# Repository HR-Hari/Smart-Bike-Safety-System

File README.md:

# Smart Bike Safety System

A **Smart Bike Safety System** for motor bikes using a **dual-microcontroller architecture**.  
The system detects theft attempts, abnormal movement, crash events, and **rider alcohol consumption**, sends **real-time alerts with GPS location** to the owner via **GSM**, and can **remotely disable the engine** for enhanced safety and security.

## Project Overview

Motor bike theft, unsafe riding, and delayed accident response remain major challenges.  
This project presents a **smart embedded safety and anti-theft solution** using **ESP32-based controllers**, inertial sensing, alcohol detection, GPS tracking, and GSM communication.

The system is divided into:

- **Master Unit (ESP32)** – Handles GPS tracking, GSM communication, crash detection, theft response, and engine cutoff.  
- **Slave Unit (ESP32-C3 Mini)** – Dedicated to rider safety monitoring, including alcohol detection and environmental sensing.

This modular design improves **reliability, power efficiency, fault isolation, and scalability**.

## System Functionality & Working

The Smart Bike Safety System operates using a **distributed dual-controller architecture** to ensure reliable monitoring and fast response. The **ESP32 Master unit**, powered directly from the bike battery, acts as the central control node responsible for decision-making, communication, and engine control. It interfaces with a **SIM900A GSM module** for SMS alerts, a **NEO-M8N GPS module** for real-time location tracking, a **5V relay** for engine cutoff, and an **MPU6050 inertial sensor** for detecting crash events and abnormal vehicle motion.

A secondary **ESP32-C3 Mini Slave unit**, powered by a rechargeable 5V battery, focuses on **rider safety monitoring**. It continuously measures alcohol concentration using the **MQ-3 alcohol sensor** and environmental conditions using the **DHT22 temperature and humidity sensor**. The Slave unit communicates safety status data wirelessly to the Master using **ESP-NOW**, enabling low-latency and power-efficient data transfer without relying on external networks.

During operation, the system continuously evaluates inputs from both controllers. If **alcohol consumption exceeds a predefined threshold**, a **crash is detected**, or **unauthorized movement** is identified, the Master unit immediately retrieves GPS coordinates and sends an **SMS alert via GSM** to the registered user. In critical scenarios, the system activates the **engine cutoff relay**, preventing the bike from being started or continuing operation. This integrated approach ensures **theft prevention, rider safety, and rapid incident notification** in a single embedded solution.

## Objectives

- Detect unauthorized movement or theft attempts  
- Detect crash events using inertial sensing  
- Detect rider alcohol consumption before or during riding  
- Send real-time SMS alerts with GPS location  
- Remotely disable the bike engine when unsafe conditions are detected  
- Implement a low-cost, embedded IoT-based safety system  

## System Architecture
            ┌────────────────────────────┐
            │        ESP32 MASTER        │
            │─────────────────────────── │
            │ • GSM (SIM900A)            │
            │ • GPS (NEO-M8N)            │
            │ • MPU6050 (Crash Detection)│
            │ • Engine Cutoff Relay      │
            │ • Alert & Control Logic    │
            └───────────▲────────────────┘
                        │ ESP-NOW
            ┌───────────┴────────────────┐
            │       ESP32-C3 MINI SLAVE  │
            │────────────────────────────│
            │ • MQ-3 (Alcohol Detection) │
            │ • DHT22 (Temp & Humidity)  │
            │ • Rider Safety Monitoring  │
            └────────────────────────────┘

## Hardware Components

### Master Unit (ESP32)

| Component | Description |
|---------|------------|
| ESP32 | Main controller |
| SIM900A GSM Module | SMS alert communication |
| NEO-M8N GPS Module | Real-time location tracking |
| MPU6050 | Crash and abnormal motion detection |
| 5V Relay Module | Engine cutoff control |
| Power Source | Motor bike 12V battery (regulated) |

### Slave Unit (ESP32-C3 Mini)

| Component | Description |
|---------|------------|
| ESP32-C3 Mini | Secondary controller |
| MQ-3 Alcohol Sensor | Rider alcohol detection |
| DHT22 | Temperature & humidity monitoring |
| Power Source | 5V rechargeable battery |

## Schematic

## PCB & Enclosure Design

### Master Unit PCB Design
<table>
  <tr>
    <td>
      
    </td>
    <td>
      
    </td>
  </tr>
</table>

### Slave Unit PCB Design

<table>
  <tr>
    <td>
      
    </td>
    <td>
      
    </td>
  </tr>
</table>

### Master & Slave Enclosure / Casing

> **(Insert Master and Slave casing images here)**  
> *Show how the units are enclosed and protected for installation on the bike.*

## Software & Technologies

- **Programming Language**: C / C++
- **IDE**: Arduino IDE
- **Wireless Communication**:
  - ESP-NOW (ESP32 ↔ ESP32-C3)
- **Serial Communication**:
  - UART (ESP32 ↔ GSM)
  - UART (ESP32 ↔ GPS)
- **Core Concepts**:
  - Embedded Systems
  - IoT-based Vehicle Safety
  - Sensor Interfacing
  - Real-time Event Detection
  - Power Management

## Key Features

- Theft detection through abnormal motion analysis  
- Crash detection using MPU6050  
- Alcohol detection using MQ-3 sensor  
- Environmental monitoring using DHT22  
- GPS-based real-time location sharing  
- SMS alerts via GSM (SIM900A)  
- Engine immobilization using relay  
- Dual power supply for uninterrupted operation  

## Project Structure

## Testing & Validation

- Unauthorized movement and theft detection  
- Crash detection sensitivity tuning  
- Alcohol threshold calibration  
- GSM SMS delivery reliability  
- GPS fix accuracy and response time  
- Engine cutoff activation timing  

System validated under real motor bike operating conditions.

## Future Enhancements

- Mobile application integration  
- Cloud-based real-time tracking dashboard  
- Rider authentication using BLE or RFID  
- Geofencing alerts  
- AI-based rider behavior analysis

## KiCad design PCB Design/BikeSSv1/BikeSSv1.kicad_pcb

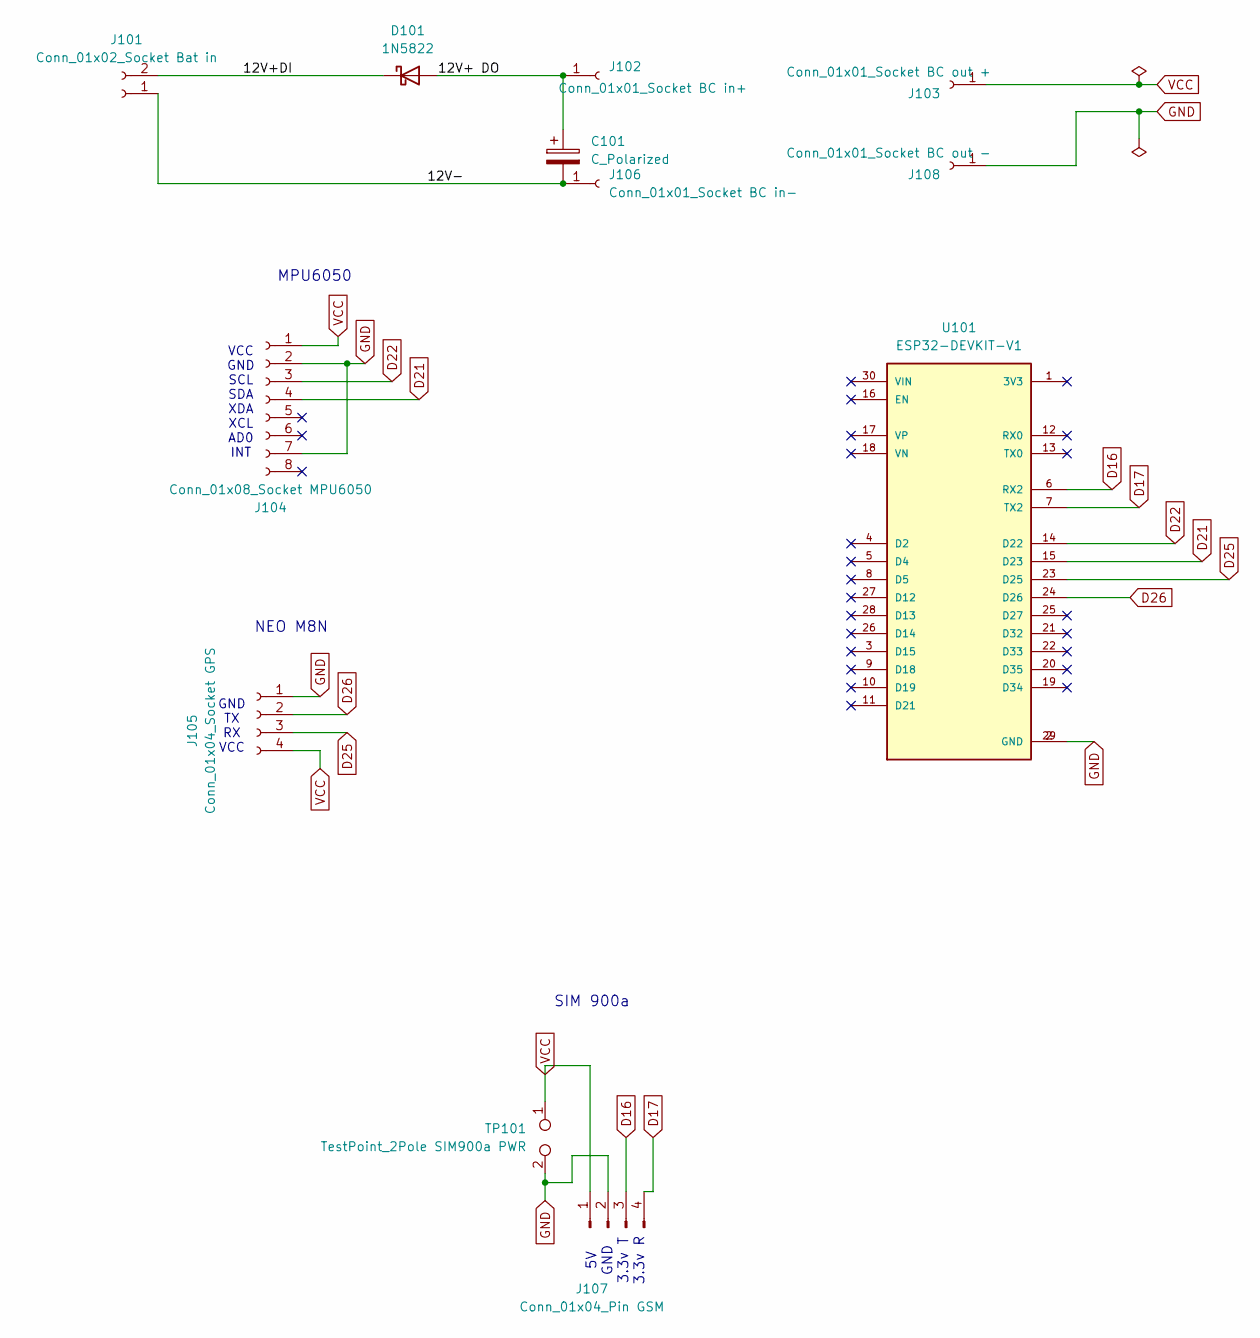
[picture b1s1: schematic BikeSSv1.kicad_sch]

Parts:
C101: C_Polarized; CP_Radial_D8.0mm_P3.50mm
D101: 1N5822; D_DO-201AD_P15.24mm_Horizontal
J101: Conn_01x02_Socket Bat in; JST_XH_B2B-XH-AM_1x02_P2.50mm_Vertical
J102: Conn_01x01_Socket BC in+; PinSocket_1x01_P2.54mm_Vertical
J103: Conn_01x01_Socket BC out +; PinSocket_1x01_P2.54mm_Vertical
J104: Conn_01x08_Socket MPU6050; PinSocket_1x08_P2.54mm_Vertical
J105: Conn_01x04_Socket GPS; PinSocket_1x04_P2.54mm_Vertical
J106: Conn_01x01_Socket BC in-; PinSocket_1x01_P2.54mm_Vertical
J107: Conn_01x04_Pin GSM; PinSocket_1x04_P2.54mm_Vertical
J108: Conn_01x01_Socket BC out -; PinSocket_1x01_P2.54mm_Vertical
TP101: TestPoint_2Pole SIM900a PWR; TestPoint_2Pads_Pitch5.08mm_Drill1.3mm
U101: ESP32-DEVKIT-V1; MODULE_ESP32_DEVKIT_V1; PARTREV N/A

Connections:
/12V+ DO: C101.1, D101.2 (A), J102.1
/12V+DI: D101.1 (K), J101.2
/12V-: C101.2, J101.1, J106.1
D16: J107.3, U101.6 (RX2)
D17: J107.4, U101.7 (TX2)
D21: J104.4, U101.15 (D23)
D22: J104.3, U101.14 (D22)
D25: J105.3, U101.23 (D25)
D26: J105.2, U101.24 (D26)
GND: J104.2, J104.7, J105.1, J107.2, J108.1, TP101.2, U101.2 (GND), U101.29 (GND)
VCC: J103.1, J104.1, J105.4, J107.1, TP101.1

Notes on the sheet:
VCC GND SCL SDA XDA XCL AD0 INT
5V GND 3.3v T 3.3v R
SIM 900a
NEO M8N
GND TX RX VCC
MPU6050

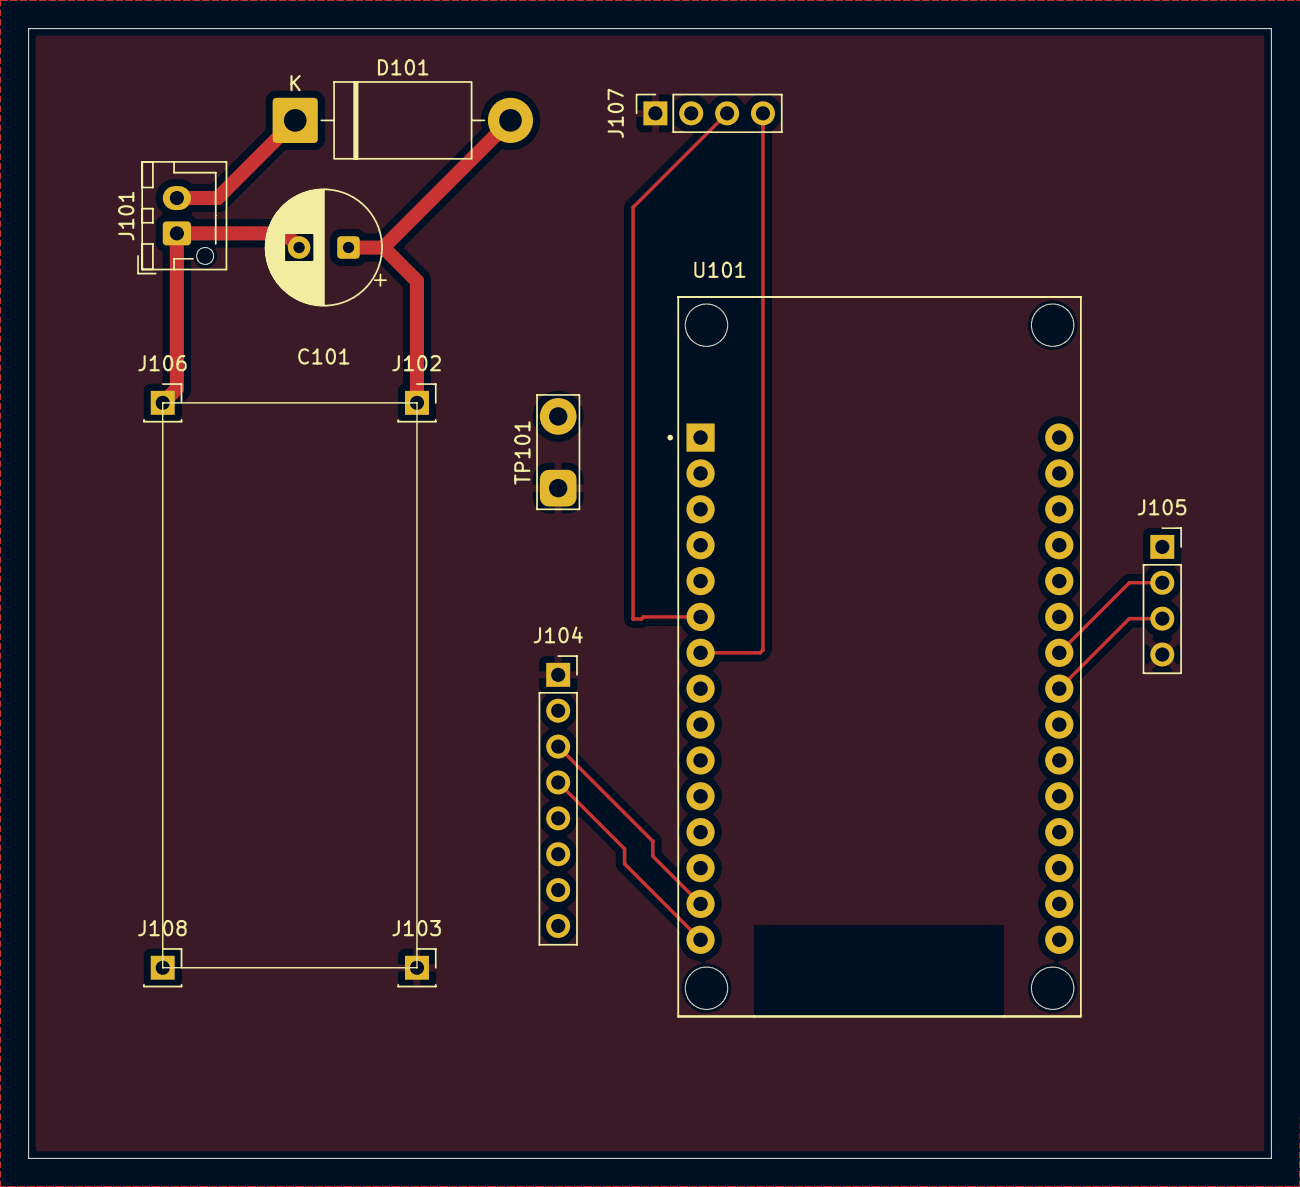
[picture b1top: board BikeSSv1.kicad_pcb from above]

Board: 2 copper layers, 88.0 x 80.0 mm, 12 parts (0 on the bottom side), 11 nets.

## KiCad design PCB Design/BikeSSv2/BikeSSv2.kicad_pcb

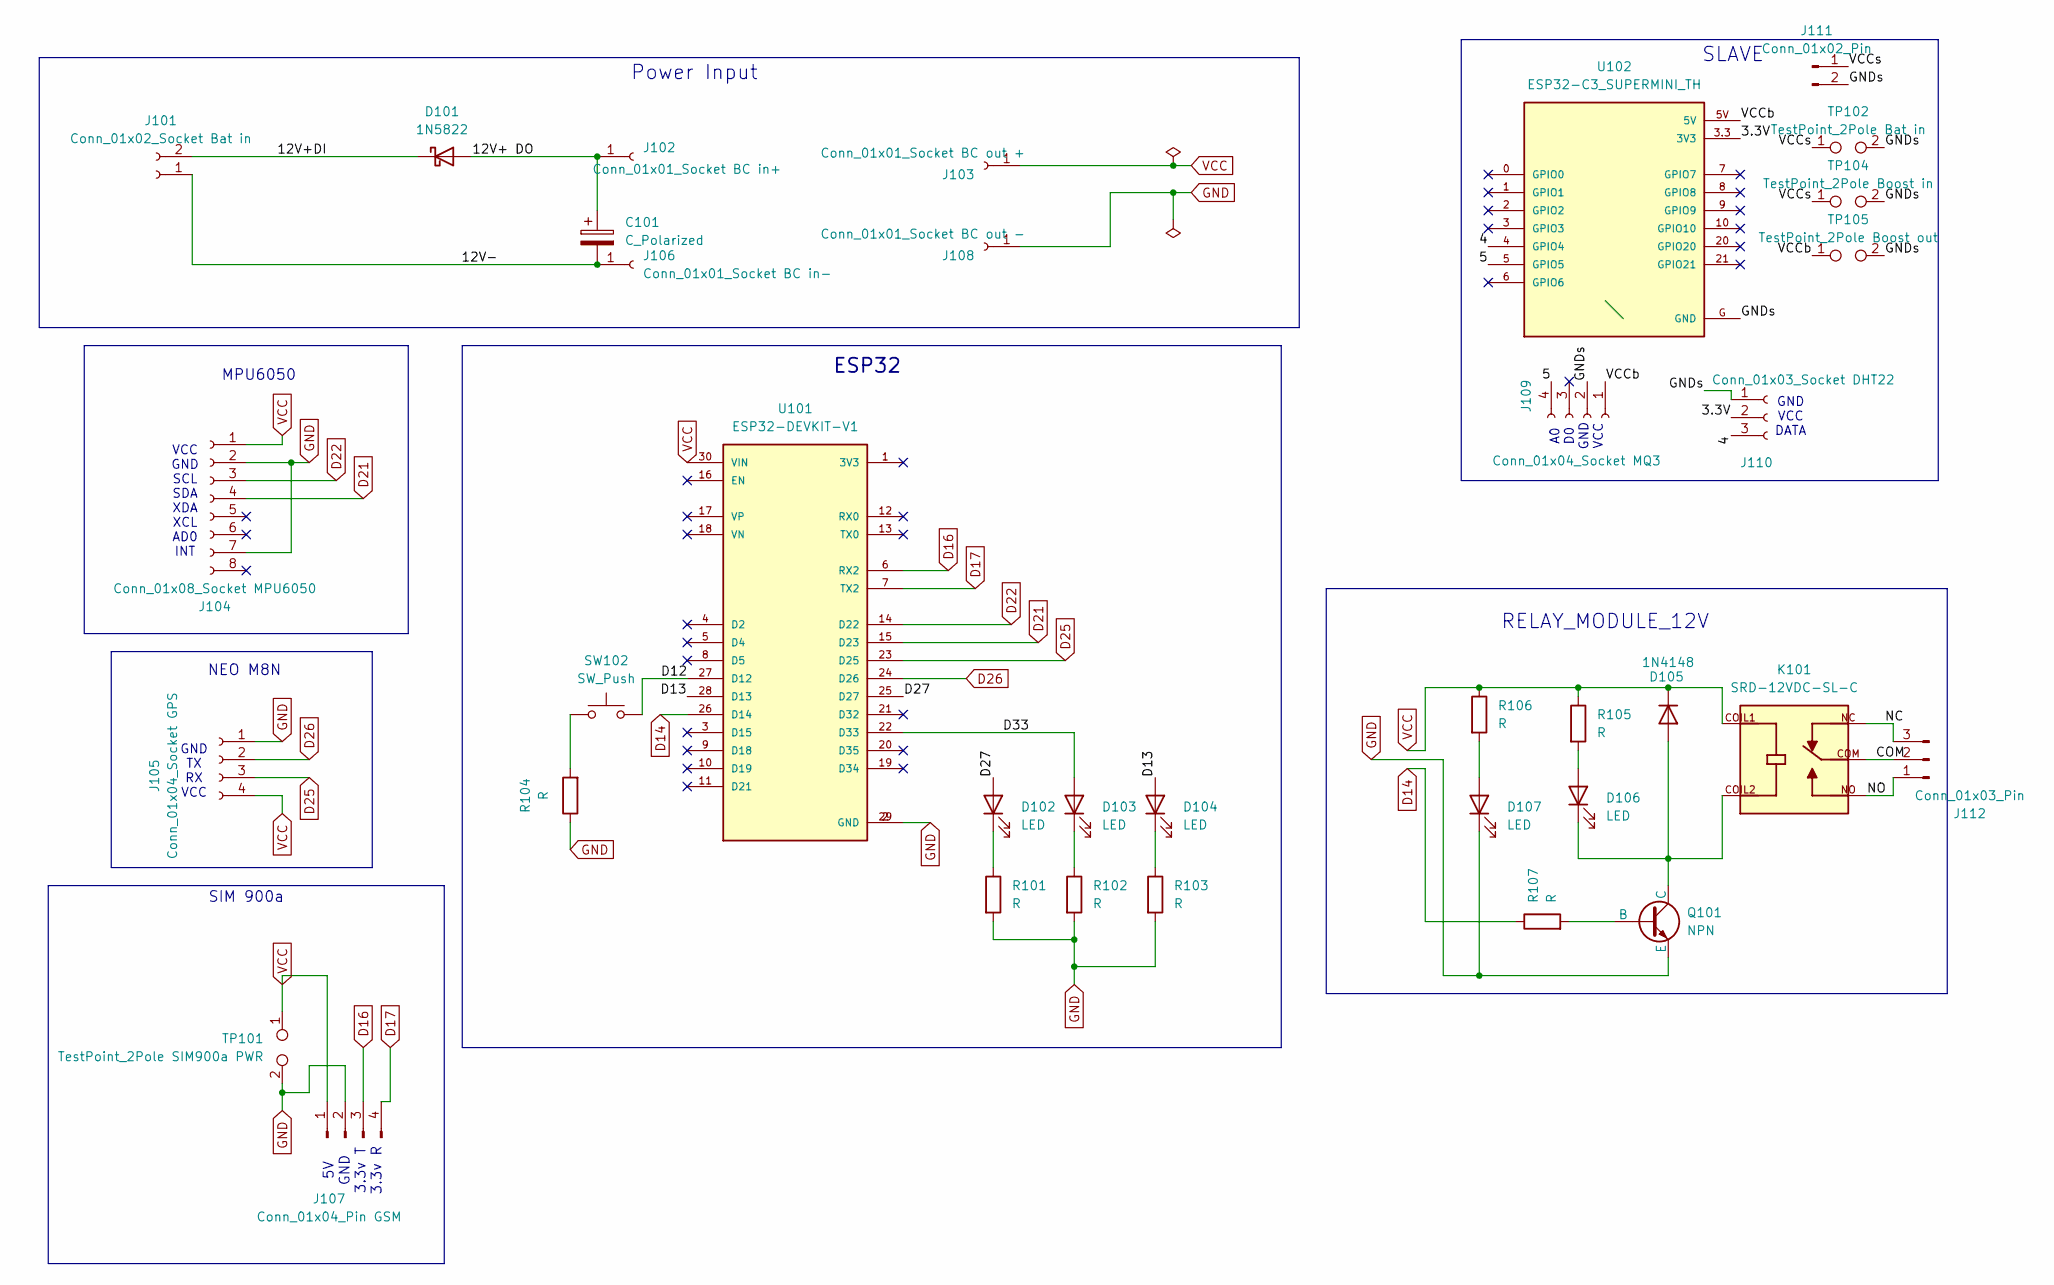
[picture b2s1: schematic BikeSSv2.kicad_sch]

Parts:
C101: C_Polarized; CP_Radial_D8.0mm_P3.50mm
D101: 1N5822; D_DO-201AD_P15.24mm_Horizontal
D102, D103, D104, D106, D107: LED; LED_D3.0mm_Clear
D105: 1N4148; D_DO-35_SOD27_P7.62mm_Horizontal
J101: Conn_01x02_Socket Bat in; JST_XH_B2B-XH-AM_1x02_P2.50mm_Vertical
J102: Conn_01x01_Socket BC in+; PinSocket_1x01_P2.54mm_Vertical
J103: Conn_01x01_Socket BC out +; PinSocket_1x01_P2.54mm_Vertical
J104: Conn_01x08_Socket MPU6050; PinSocket_1x08_P2.54mm_Vertical
J105: Conn_01x04_Socket GPS; PinSocket_1x04_P2.54mm_Vertical
J106: Conn_01x01_Socket BC in-; PinSocket_1x01_P2.54mm_Vertical
J107: Conn_01x04_Pin GSM; PinSocket_1x04_P2.54mm_Vertical
J108: Conn_01x01_Socket BC out -; PinSocket_1x01_P2.54mm_Vertical
J109: Conn_01x04_Socket MQ3; PinSocket_1x04_P2.54mm_Horizontal
J110: Conn_01x03_Socket DHT22; PinSocket_1x03_P2.54mm_Vertical
J111: Conn_01x02_Pin; JST_XH_S2B-XH-A-1_1x02_P2.50mm_Horizontal
J112: Conn_01x03_Pin; Samtec_HPM-03-05-x-S_Straight_1x03_Pitch5.08mm
K101: SRD-12VDC-SL-C; RELAY_SRD-12VDC-SL-C; PARTREV 1.0
Q101: NPN; TO-92L_Wide
R101, R102, R103, R104, R105, R106, R107: R; R_Axial_DIN0204_L3.6mm_D1.6mm_P7.62mm_Horizontal
SW102: SW_Push; SW_PUSH-12mm
TP101: TestPoint_2Pole SIM900a PWR; TestPoint_2Pads_Pitch5.08mm_Drill1.3mm
TP102: TestPoint_2Pole Bat in; Battery_Charger_TD4056_Module
TP104: TestPoint_2Pole Boost in; TestPoint_2Pads_Pitch7mm_Drill1.3mm
TP105: TestPoint_2Pole Boost out; TestPoint_2Pads_Pitch7mm_Drill1.3mm
U101: ESP32-DEVKIT-V1; MODULE_ESP32_DEVKIT_V1; PARTREV N/A
U102: ESP32-C3_SUPERMINI_TH; MODULE_ESP32-C3_SUPERMINI_TH

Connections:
/3.3V: J110.2, U102.3.3 (3V3)
/4: J110.3, U102.4 (GPIO4)
/5: J109.4, U102.5 (GPIO5)
/12V+ DO: C101.1, D101.2 (A), J102.1
/12V+DI: D101.1 (K), J101.2
/12V-: C101.2, J101.1, J106.1
/D12: SW102.2, U101.27 (D12)
/D13: D104.2 (A), U101.28 (D13)
/D27: D102.2 (A), U101.25 (D27)
/D33: D103.2 (A), U101.22 (D33)
/GNDs: J109.2, J110.1, J111.2, TP102.2, TP104.2, TP105.2, U102.G (GND)
/VCCb: J109.1, TP105.1, U102.5V
/VCCs: J111.1, TP102.1, TP104.1
D14: R107.1, U101.26 (D14)
D16: J107.3, U101.6 (RX2)
D17: J107.4, U101.7 (TX2)
D21: J104.4, U101.15 (D23)
D22: J104.3, U101.14 (D22)
D25: J105.3, U101.23 (D25)
D26: J105.2, U101.24 (D26)
GND: D107.1 (K), J104.2, J104.7, J105.1, J107.2, J108.1, Q101.3 (E), R101.2, R102.2, R103.2, R104.1, TP101.2, U101.2 (GND), U101.29 (GND)
unnamed: D102.1 (K), R101.1
unnamed: D103.1 (K), R102.1
unnamed: D104.1 (K), R103.1
unnamed: D105.2 (A), D106.1 (K), K101.COIL2, Q101.1 (C)
unnamed: D106.2 (A), R105.2
unnamed: D107.2 (A), R106.2
unnamed: J112.1, K101.NO
unnamed: J112.2, K101.COM
unnamed: J112.3, K101.NC
unnamed: Q101.2 (B), R107.2
unnamed: R104.2, SW102.1
VCC: D105.1 (K), J103.1, J104.1, J105.4, J107.1, K101.COIL1, R105.1, R106.1, TP101.1, U101.30 (VIN)

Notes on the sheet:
SLAVE
A0 D0 GND VCC
VCC GND SCL SDA XDA XCL AD0 INT
RELAY_MODULE_12V
ESP32
5V GND 3.3v T 3.3v R
SIM 900a
NEO M8N
GND TX RX VCC
GND VCC DATA
Power Input
MPU6050

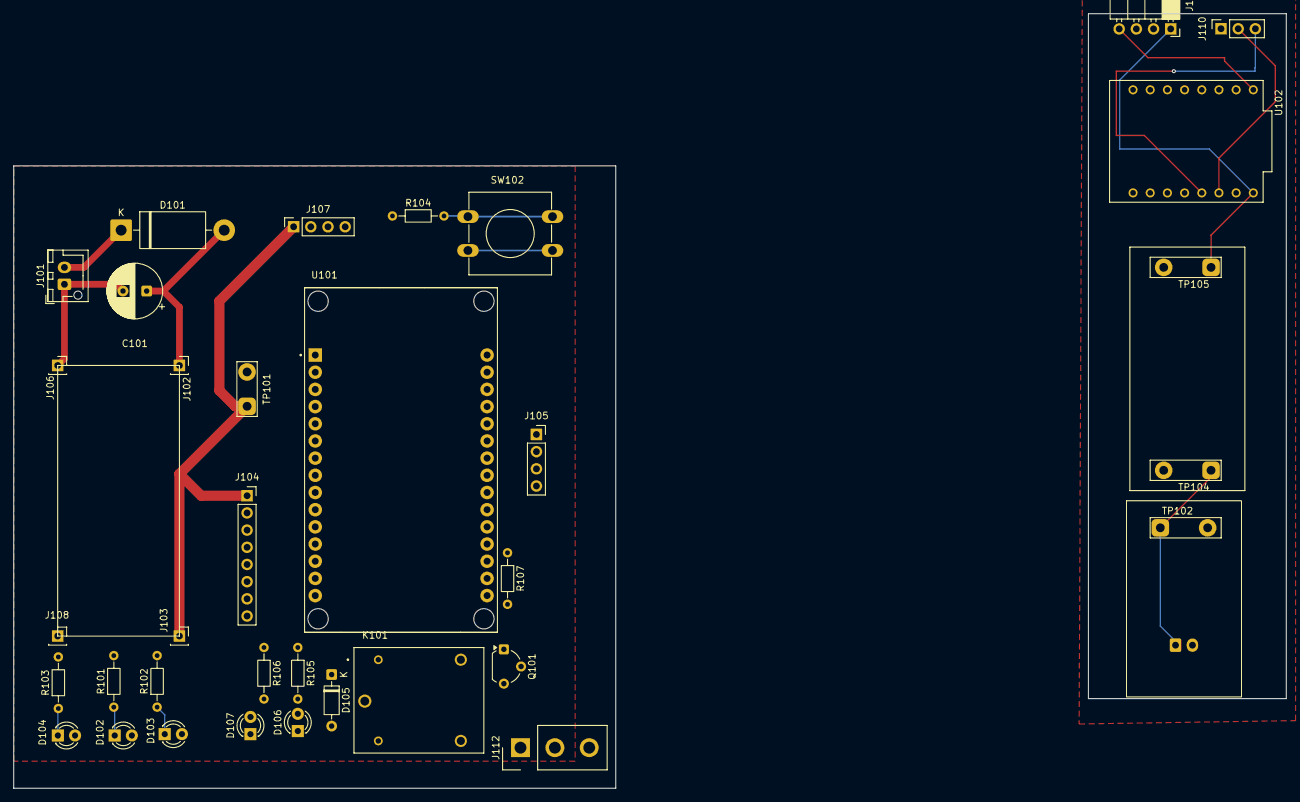
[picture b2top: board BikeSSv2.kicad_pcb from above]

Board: 2 copper layers, 188.1 x 114.5 mm, 36 parts (1 on the bottom side), 33 nets.

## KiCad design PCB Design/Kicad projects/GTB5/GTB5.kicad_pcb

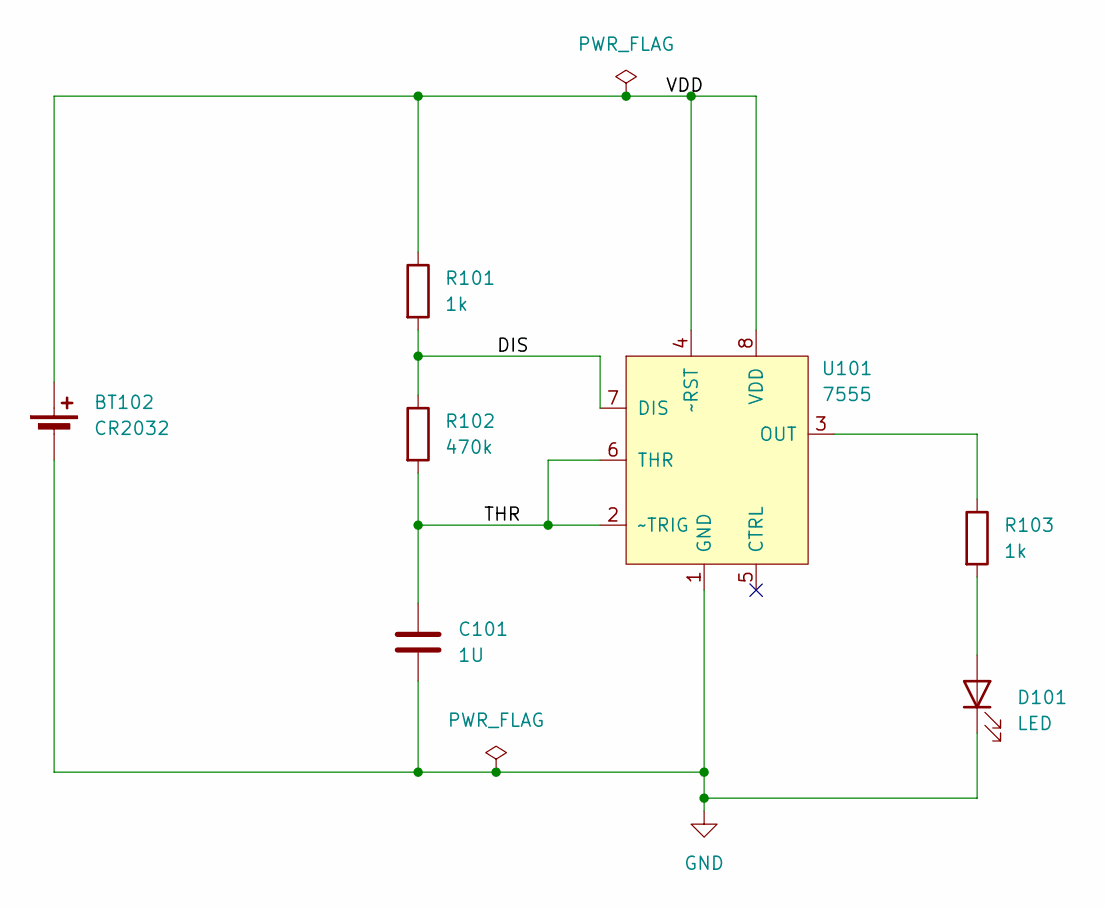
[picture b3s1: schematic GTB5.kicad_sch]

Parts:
BT102: CR2032; S8211-46R
C101: 1U; C_0805_2012Metric_Pad1.18x1.45mm_HandSolder
D101: LED; LED_0805_2012Metric_Pad1.15x1.40mm_HandSolder
R101, R103: 1k; R_0805_2012Metric_Pad1.20x1.40mm_HandSolder
R102: 470k; R_0805_2012Metric_Pad1.20x1.40mm_HandSolder
U101: 7555; SOIC-8_3.9x4.9mm_P1.27mm

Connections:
/DIS: R101.2, R102.1, U101.7 (DIS)
/THR: C101.1, R102.2, U101.2 (~TRIG), U101.6 (THR)
/VDD: BT102.1 (+), R101.1, U101.4 (~RST), U101.8 (VDD)
GND: BT102.2 (-), C101.2, D101.1 (K), U101.1 (GND)
unnamed: D101.2 (A), R103.2
unnamed: R103.1, U101.3 (OUT)

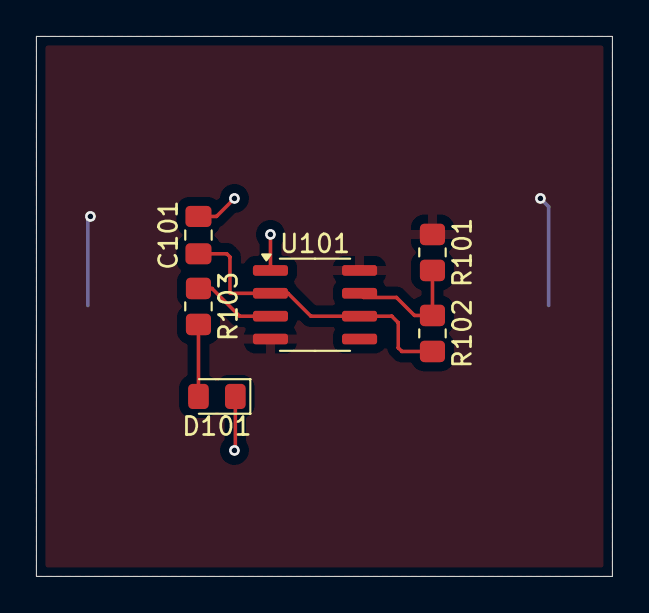
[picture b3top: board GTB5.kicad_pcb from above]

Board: 2 copper layers, 32.0 x 30.0 mm, 7 parts (1 on the bottom side), 6 nets.

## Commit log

2026-01-20 Readme updated
2026-01-20 PCB & 3D Design
2026-01-20 casing image
2026-01-20 Update Casing Images
